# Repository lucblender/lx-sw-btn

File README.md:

# lx-sw-btn

This repository contains the KiCad project for the "lx-sw-btn": a 2HP eurorack module with 4 customizable switches enabled CV outputs!

With two buttons and two switches, the lx-sw-btn enables four CV "on-off" outputs. By default, the output is set to 0-5V, but each output can be fine-tuned through front-panel adjustment holes ranging from -10V to +10V. This will allow you to use the switches not only as triggers but also for precise CV control.

The module is extremely compact with only a single PCB featuring SMD components on both sides, ensuring no wasted space!

I used [PCBWay](pcbway.com) services were used for the PCB manufacturing, both pcb and front panel.

## Content

Under the [hardware](/hardware/) folder, you will find the KiCad project with the following files:

- [Project](/hardware/2hp-simple-switch-button/2hp-simple-switch-button.kicad_pro)
- [Schematic](/hardware/2hp-simple-switch-button/2hp-simple-switch-button.kicad_sch)
- [Main PCB](/hardware/2hp-simple-switch-button/2hp-simple-switch-button.kicad_pcb)
- [Front panel PCB](/hardware/2hp-simple-switch-button/2hp-simple-switch-button-front-panel.kicad_pcb)

## Circuit

The circuit consist of 4 times the circuit below: an opamp as follower with a voltage devider between VCC and VEE as input through a potentiometer. The output is set to 1k impedance with a RC filter useful for debouncing the switches and buttons.

The module also have power supply invert polarity protection and input filtering.

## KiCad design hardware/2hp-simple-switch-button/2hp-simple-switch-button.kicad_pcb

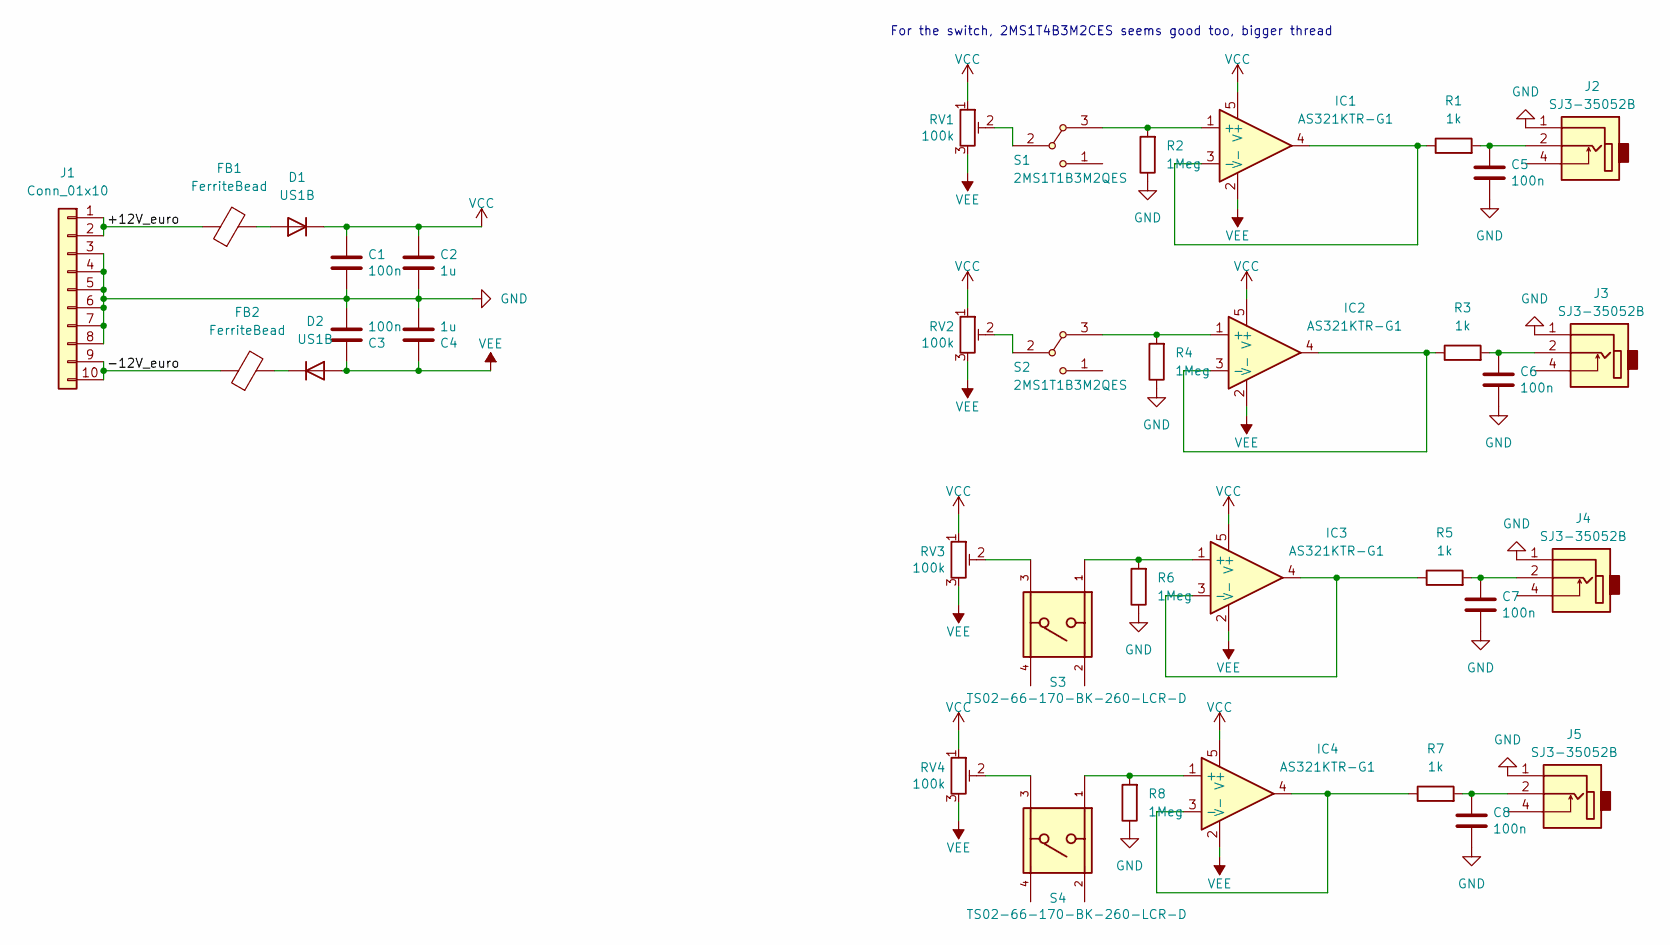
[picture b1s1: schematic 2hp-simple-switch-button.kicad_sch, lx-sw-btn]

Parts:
C1, C3, C5, C6, C7, C8: 100n; C_0603_1608Metric; Mouser Part Number 581-06031C104MAT2A; LCSC C14663
C2, C4: 1u; C_0603_1608Metric; Mouser Part Number 187-CL10B105KO8NNWC; LCSC C14663
D1, D2: US1B; D_SMA; Mouser Part Number 637-US1B
FB1, FB2: FerriteBead; L_0805_2012Metric; Mouser Part Number 710-742792031
IC1, IC2, IC3, IC4: AS321KTR-G1; SOT95P282X145-5N; Mouser Part Number 621-AS321KTR-G1
J1: Conn_01x10; PinHeader_2x05_P2.54mm_Vertical_SMD; Mouser Part Number 200-TSM10501LDVPTR
J2, J3, J4, J5: SJ3-35052B; SJ335052B; Mouser Part Number 179-SJ3-35052B
R1, R3, R5, R7: 1k; R_0805_2012Metric; Mouser Part Number RT0805FRE071KL
R2, R4, R6, R8: 1Meg; R_0805_2012Metric; Mouser Part Number 72-TS53YL-100K
RV1, RV2, RV3, RV4: 100k; Potentiometer_Vishay_TS53YL_Vertical; Mouser Part Number 72-TS53YL-100K
S1, S2: 2MS1T1B3M2QES; Mouser Part Number 118-2MS1T1B3M2QES or 118-2MS1T4B3M2CES
S3, S4: TS02-66-170-BK-260-LCR-D; SW_TS02-66-170-BK-260-LCR-D; PARTREV 1.0; Mouser Part Number 179-TS0266170BK260LC

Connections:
/+12V_euro: FB1.1, J1.1, J1.2
/-12V_euro: FB2.1, J1.9, J1.10
GND: C1.2, C2.2, C3.2, C4.2, C5.2, C6.2, C7.2, C8.2, J1.3, J1.4, J1.5, J1.6, J1.7, J1.8, J2.1, J3.1, J4.1, J5.1, R2.1, R4.1, R6.1, R8.1
unnamed: C5.1, J2.2, R1.2
unnamed: C6.1, J3.2, R3.2
unnamed: C7.1, J4.2, R5.2
unnamed: C8.1, J5.2, R7.2
unnamed: D1.2 (A), FB1.2
unnamed: D2.1 (K), FB2.2
unnamed: IC1.1 (+), R2.2, S1.3
unnamed: IC1.3 (-), IC1.4, R1.1
unnamed: IC2.1 (+), R4.2, S2.3
unnamed: IC2.3 (-), IC2.4, R3.1
unnamed: IC3.1 (+), R6.2, S3.1
unnamed: IC3.3 (-), IC3.4, R5.1
unnamed: IC4.1 (+), R8.2, S4.1
unnamed: IC4.3 (-), IC4.4, R7.1
unnamed: RV1.2, S1.2
unnamed: RV2.2, S2.2
unnamed: RV3.2, S3.3
unnamed: RV4.2, S4.3
VCC: C1.1, C2.1, D1.1 (K), IC1.5 (V+), IC2.5 (V+), IC3.5 (V+), IC4.5 (V+), RV1.1, RV2.1, RV3.1, RV4.1
VEE: C3.1, C4.1, D2.2 (A), IC1.2 (V-), IC2.2 (V-), IC3.2 (V-), IC4.2 (V-), RV1.3, RV2.3, RV3.3, RV4.3

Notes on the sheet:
For the switch, 2MS1T4B3M2CES seems good too, bigger thread

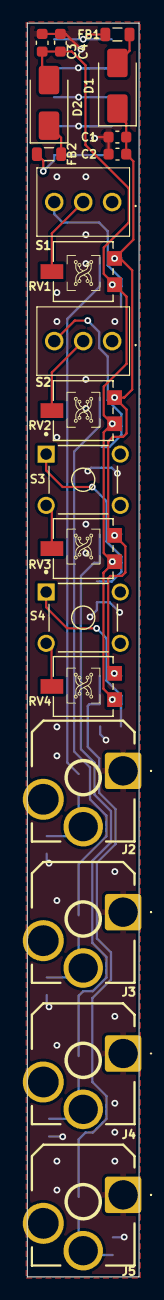
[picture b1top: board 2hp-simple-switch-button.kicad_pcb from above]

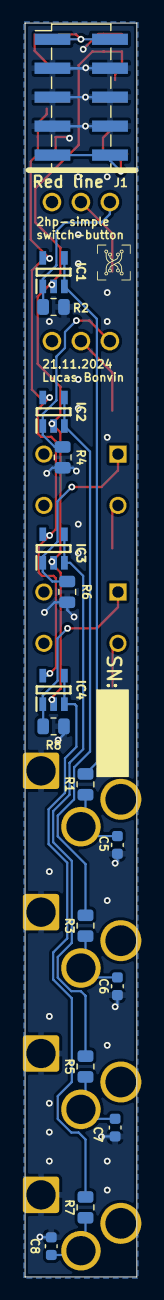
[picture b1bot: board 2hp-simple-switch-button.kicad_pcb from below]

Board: 2 copper layers, 9.8 x 110.0 mm, 37 parts (17 on the bottom side), 23 nets.

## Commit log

2025-01-02 feature: inital project commit
2025-01-02 fix: fix picture
